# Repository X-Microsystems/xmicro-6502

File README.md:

# XMICRO-6502

W65C02 CPU card for the [XMICRO Bus](https://github.com/X-Microsystems/xmicro-bus).

Datasheet: [XMICRO-6502](Documentation/XMICRO-6502.pdf)

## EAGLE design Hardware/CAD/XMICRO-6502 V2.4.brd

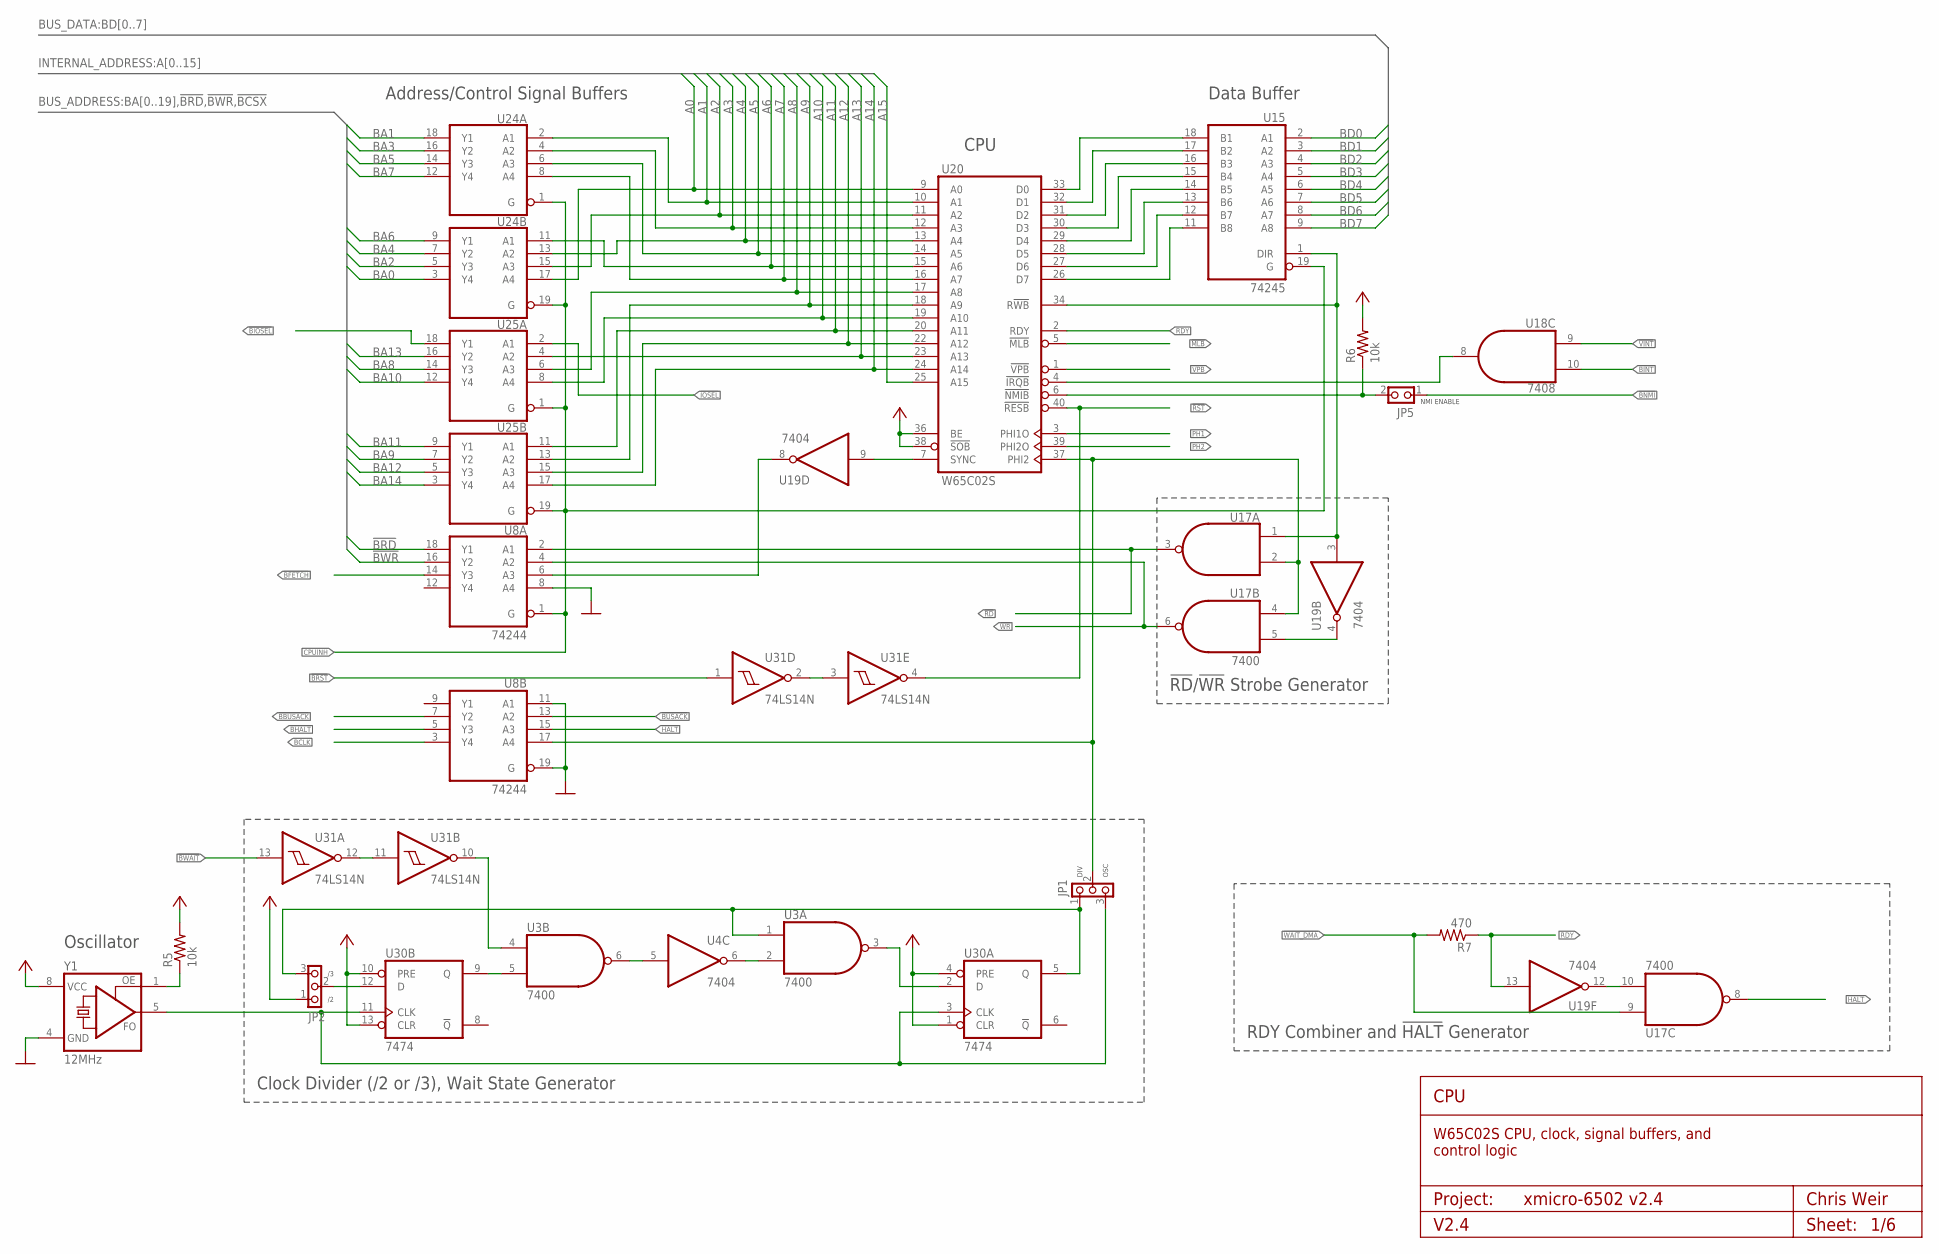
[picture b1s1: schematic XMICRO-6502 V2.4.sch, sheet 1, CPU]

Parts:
JP1, JP2: PINHD1X3THRU; 1X03
JP5: PINHD-1X2THRU; 1X02
R5, R6: 10k; 0207/10
R7: 470; 0207/10
U3, U17: 7400; DIL14
U4, U19: 7404; DIL14
U8, U24, U25: 74244; DIL20
U15: 74245; DIL20
U18: 7408; DIL14
U20: W65C02S; DIL40
U30: 7474; DIL14
U31: 74LS14N; DIL14
Y1: 12MHz; DIL08S

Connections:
!BBUSACK: U8.7 (Y2); also elsewhere on the board
!BFETCH: U8.14 (Y3); also elsewhere on the board
!BHALT: U8.5 (Y3); also elsewhere on the board
!BINT: U18.10 (I1); also elsewhere on the board
!BIOSEL: U25.18 (Y1); also elsewhere on the board
!BNMI: JP5.1; also elsewhere on the board
!BRD: U8.18 (Y1); also elsewhere on the board
!BRST: U31.1 (I); also elsewhere on the board
!BUSACK: U8.13 (A2); also elsewhere on the board
!BWAIT: U31.13 (I); also elsewhere on the board
!BWR: U8.16 (Y2); also elsewhere on the board
!CINT: U18.8 (O), U20.4 (!IRQB)
!HALT: U8.15 (A3), U17.8 (O); also elsewhere on the board
!IOSEL: U25.2 (A1); also elsewhere on the board
!MLB: U20.5 (!MLB); also elsewhere on the board
!RD: U8.2 (A1), U17.3 (O); also elsewhere on the board
!RST: U20.40 (!RESB), U31.4 (O); also elsewhere on the board
!VINT: U18.9 (I0); also elsewhere on the board
!VPB: U20.1 (!VPB); also elsewhere on the board
!WAIT_DMA: R7.2, U17.9 (I0); also elsewhere on the board
!WR: U8.4 (A2), U17.6 (O)
A0: U20.9 (A0), U24.17 (A4); also elsewhere on the board
A1: U20.10 (A1), U24.2 (A1); also elsewhere on the board
A2: U20.11 (A2), U24.15 (A3); also elsewhere on the board
A3: U20.12 (A3), U24.4 (A2)
A4: U20.13 (A4), U24.13 (A2)
A5: U20.14 (A5), U24.6 (A3)
A6: U20.15 (A6), U24.11 (A1)
A7: U20.16 (A7), U24.8 (A4)
A8: U20.17 (A8), U25.6 (A3)
A9: U20.18 (A9), U25.13 (A2); also elsewhere on the board
A10: U20.19 (A10), U25.8 (A4); also elsewhere on the board
A11: U20.20 (A11), U25.11 (A1); also elsewhere on the board
A12: U20.22 (A12), U25.15 (A3); also elsewhere on the board
A13: U20.23 (A13), U25.4 (A2); also elsewhere on the board
A14: U20.24 (A14), U25.17 (A4); also elsewhere on the board
A15: U20.25 (A15); also elsewhere on the board
BA0: U24.3 (Y4); also elsewhere on the board
BA1: U24.18 (Y1); also elsewhere on the board
BA2: U24.5 (Y3); also elsewhere on the board
BA3: U24.16 (Y2); also elsewhere on the board
BA4: U24.7 (Y2); also elsewhere on the board
BA5: U24.14 (Y3); also elsewhere on the board
BA6: U24.9 (Y1); also elsewhere on the board
BA7: U24.12 (Y4); also elsewhere on the board
BA8: U25.14 (Y3); also elsewhere on the board
BA9: U25.7 (Y2); also elsewhere on the board
BA10: U25.12 (Y4); also elsewhere on the board
BA11: U25.9 (Y1); also elsewhere on the board
BA12: U25.5 (Y3); also elsewhere on the board
BA13: U25.16 (Y2); also elsewhere on the board
BA14: U25.3 (Y4); also elsewhere on the board
BCLK: U8.3 (Y4); also elsewhere on the board
BD0: U15.2 (A1); also elsewhere on the board
BD1: U15.3 (A2); also elsewhere on the board
BD2: U15.4 (A3); also elsewhere on the board
BD3: U15.5 (A4); also elsewhere on the board
BD4: U15.6 (A5); also elsewhere on the board
BD5: U15.7 (A6); also elsewhere on the board
BD6: U15.8 (A7); also elsewhere on the board
BD7: U15.9 (A8); also elsewhere on the board
CPUINH: U8.1 (G), U15.19 (G), U24.1 (G), U24.19 (G), U25.1 (G), U25.19 (G); also elsewhere on the board
GND: U3.7 (GND), U4.7 (GND), U8.8 (A4), U8.10 (GND), U8.11 (A1), U8.19 (G), U15.10 (GND), U17.7 (GND), U18.7 (GND), U19.7 (GND), U20.21 (GND), U24.10 (GND), U25.10 (GND), U30.7 (GND), U31.7 (GND), Y1.4 (GND); also elsewhere on the board
unnamed: JP2.2, U30.12 (D)
unnamed: U17.5 (I1), U19.4 (O)
unnamed: JP1.1, JP2.3, U3.1 (I0), U30.5 (Q)
unnamed: U15.1 (DIR), U17.1 (I0), U19.3 (I), U20.34 (R!WB)
unnamed: U3.5 (I1), U30.9 (Q)
unnamed: U3.6 (O), U4.5 (I)
unnamed: R5.1, Y1.1 (OE)
unnamed: U17.10 (I1), U19.12 (O)
unnamed: U3.2 (I1), U4.6 (O)
unnamed: U15.11 (B8), U20.26 (D7)
unnamed: U15.12 (B7), U20.27 (D6)
unnamed: U15.13 (B6), U20.28 (D5)
unnamed: U15.14 (B5), U20.29 (D4)
unnamed: U15.15 (B4), U20.30 (D3)
unnamed: U15.16 (B3), U20.31 (D2)
unnamed: U15.17 (B2), U20.32 (D1)
unnamed: U15.18 (B1), U20.33 (D0)
unnamed: U31.11 (I), U31.12 (O)
unnamed: JP5.2, R6.1, U20.6 (!NMIB)
unnamed: U3.3 (O), U30.2 (D)
unnamed: JP1.3, U30.3 (CLK), U30.11 (CLK), Y1.5 (FO)
unnamed: U19.9 (I), U20.7 (SYNC)
unnamed: U8.6 (A3), U19.8 (O)
unnamed: U3.4 (I0), U31.10 (O)
unnamed: U31.2 (O), U31.3 (I)
PH0: JP1.2, U8.17 (A4), U17.2 (I1), U17.4 (I0), U20.37 (PHI2)
PH1: U20.3 (PHI1O); also elsewhere on the board
PH2: U20.39 (PHI2O); also elsewhere on the board
RDY: R7.1, U19.13 (I), U20.2 (RDY)
VCC: JP2.1, R5.2, R6.2, U3.14 (VCC), U4.14 (VCC), U8.20 (VCC), U15.20 (VCC), U17.14 (VCC), U18.14 (VCC), U19.14 (VCC), U20.8 (VCC), U20.36 (BE), U20.38 (!SOB), U24.20 (VCC), U25.20 (VCC), U30.1 (CLR), U30.4 (PRE), U30.10 (PRE), U30.13 (CLR), U30.14 (VCC), U31.14 (VCC), Y1.8 (VCC); also elsewhere on the board

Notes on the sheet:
Project:
CPU
V2.4
Chris Weir
Sheet:
W65C02S CPU, clock, signal buffers, and control logic
Address/Control Signal Buffers
Data Buffer
!RD!/!WR! Strobe Generator
Oscillator
RDY Combiner and !HALT! Generator
Clock Divider (/2 or /3), Wait State Generator
DIV
OSC
NMI ENABLE

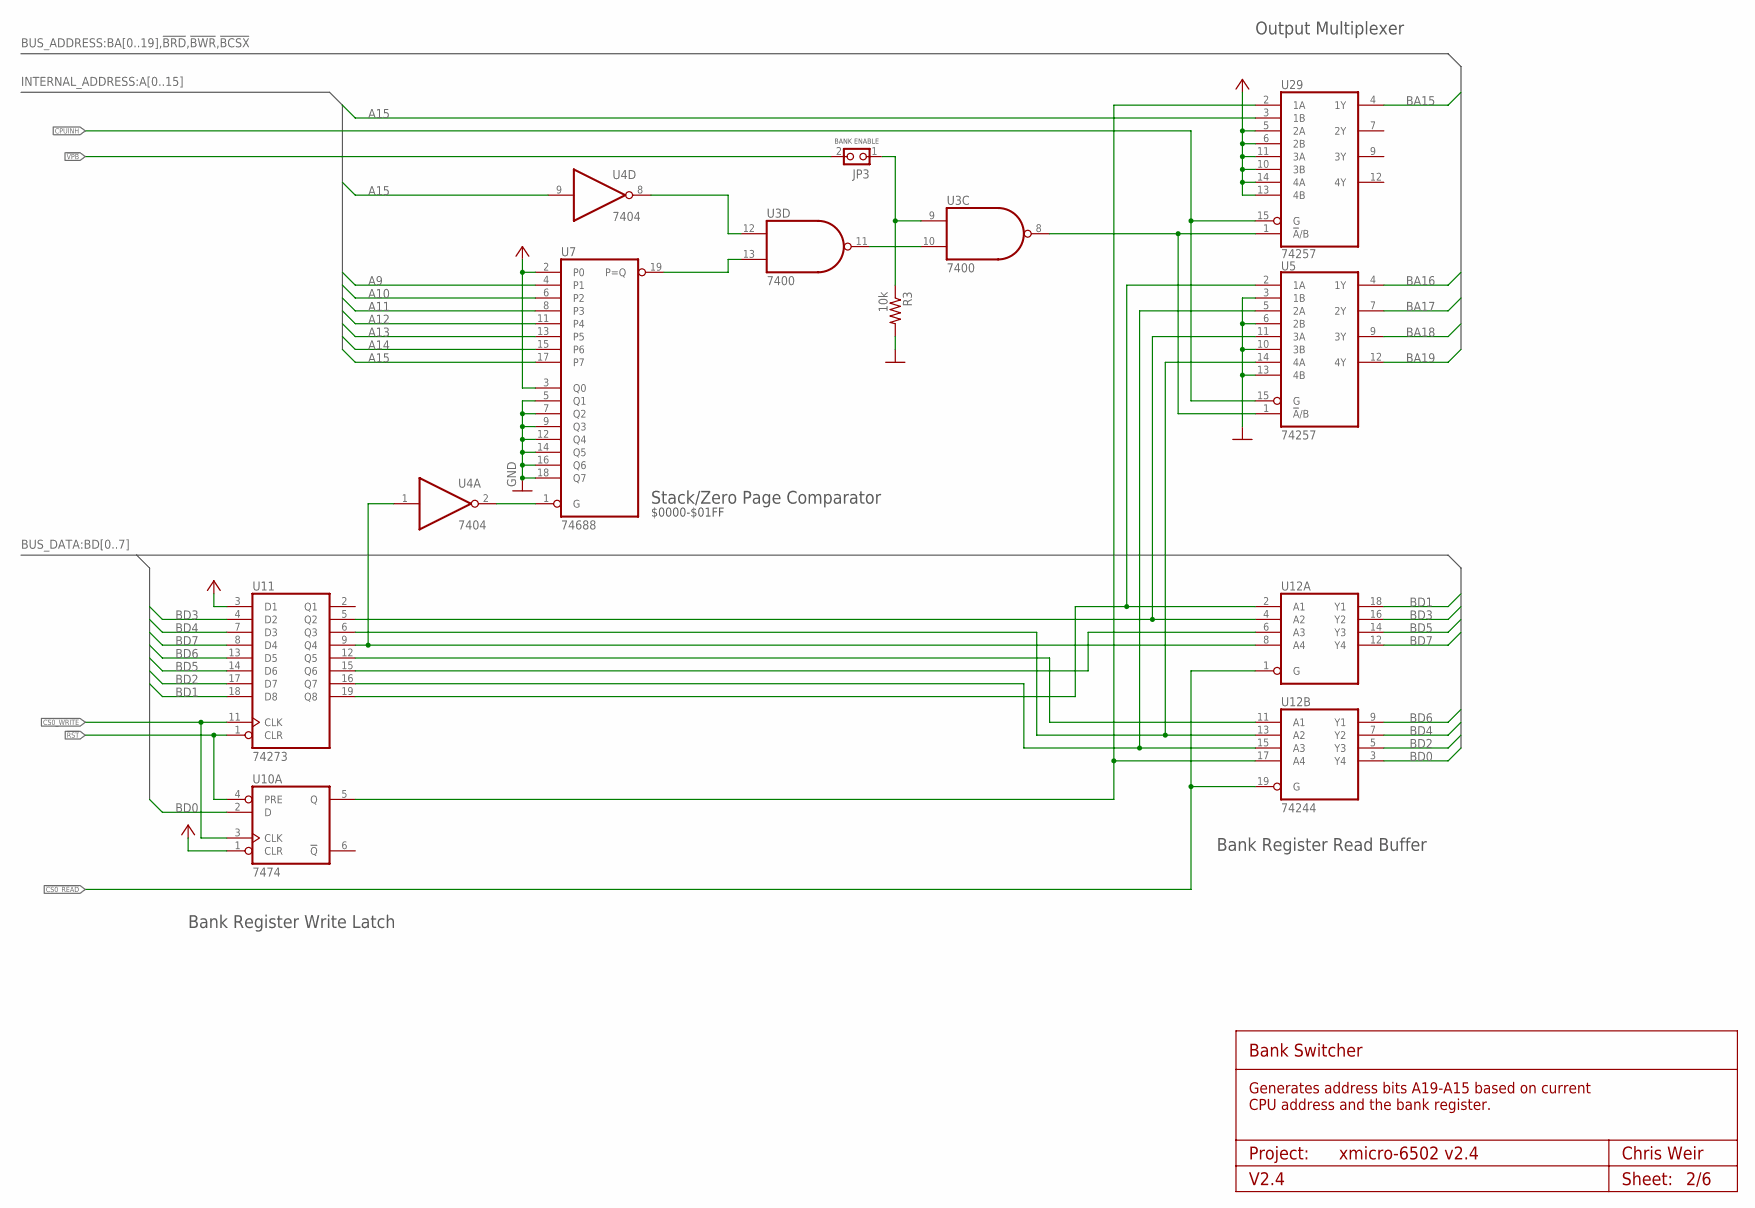
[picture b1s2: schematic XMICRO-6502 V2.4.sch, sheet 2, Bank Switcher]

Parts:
JP3: PINHD-1X2THRU; 1X02
R3: 10k; 0207/10
U3: 7400; DIL14
U4: 7404; DIL14
U5, U29: 74257; DIL16
U7: 74688; DIL20
U10: 7474; DIL14
U11: 74273; DIL20
U12: 74244; DIL20

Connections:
!CS0_READ: U12.1 (G), U12.19 (G); also elsewhere on the board
!CS0_WRITE: U10.3 (CLK), U11.11 (CLK); also elsewhere on the board
!RST: U10.4 (PRE), U11.1 (CLR); also elsewhere on the board
!VPB: JP3.2; also elsewhere on the board
A9: U7.4 (P1); also elsewhere on the board
A10: U7.6 (P2); also elsewhere on the board
A11: U7.8 (P3); also elsewhere on the board
A12: U7.11 (P4); also elsewhere on the board
A13: U7.13 (P5); also elsewhere on the board
A14: U7.15 (P6); also elsewhere on the board
A15: U4.9 (I), U7.17 (P7), U29.3 (1B); also elsewhere on the board
BA15: U29.4 (1Y); also elsewhere on the board
BA16: U5.4 (1Y); also elsewhere on the board
BA17: U5.7 (2Y); also elsewhere on the board
BA18: U5.9 (3Y); also elsewhere on the board
BA19: U5.12 (4Y); also elsewhere on the board
BD0: U10.2 (D), U12.3 (Y4); also elsewhere on the board
BD1: U11.18 (D8), U12.18 (Y1); also elsewhere on the board
BD2: U11.17 (D7), U12.5 (Y3); also elsewhere on the board
BD3: U11.4 (D2), U12.16 (Y2); also elsewhere on the board
BD4: U11.7 (D3), U12.7 (Y2); also elsewhere on the board
BD5: U11.14 (D6), U12.14 (Y3); also elsewhere on the board
BD6: U11.13 (D5), U12.9 (Y1); also elsewhere on the board
BD7: U11.8 (D4), U12.12 (Y4); also elsewhere on the board
CPUINH: U5.15 (G), U29.15 (G); also elsewhere on the board
GND: R3.2, U3.7 (GND), U4.7 (GND), U5.3 (1B), U5.6 (2B), U5.8 (GND), U5.10 (3B), U5.13 (4B), U7.5 (Q1), U7.7 (Q2), U7.9 (Q3), U7.10 (GND), U7.12 (Q4), U7.14 (Q5), U7.16 (Q6), U7.18 (Q7), U10.7 (GND), U11.10 (GND), U12.10 (GND), U29.8 (GND); also elsewhere on the board
unnamed: U5.2 (1A), U11.19 (Q8), U12.2 (A1)
unnamed: U5.11 (3A), U11.5 (Q2), U12.4 (A2)
unnamed: U5.5 (2A), U11.16 (Q7), U12.15 (A3)
unnamed: U5.14 (4A), U11.6 (Q3), U12.13 (A2)
unnamed: U3.12 (I0), U4.8 (O)
unnamed: U3.13 (I1), U7.19 (P=Q)
unnamed: U10.5 (Q), U12.17 (A4), U29.2 (1A)
unnamed: U3.10 (I1), U3.11 (O)
unnamed: JP3.1, R3.1, U3.9 (I0)
unnamed: U11.15 (Q6), U12.6 (A3)
unnamed: U3.8 (O), U5.1 (!A!/B), U29.1 (!A!/B)
unnamed: U11.12 (Q5), U12.11 (A1)
unnamed: U4.1 (I), U11.9 (Q4), U12.8 (A4)
unnamed: U4.2 (O), U7.1 (G)
VCC: U3.14 (VCC), U4.14 (VCC), U5.16 (VCC), U7.2 (P0), U7.3 (Q0), U7.20 (VCC), U10.1 (CLR), U10.14 (VCC), U11.3 (D1), U11.20 (VCC), U12.20 (VCC), U29.5 (2A), U29.6 (2B), U29.10 (3B), U29.11 (3A), U29.13 (4B), U29.14 (4A), U29.16 (VCC); also elsewhere on the board

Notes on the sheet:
$0000-$01FF
Bank Register Read Buffer
Bank Register Write Latch
Stack/Zero Page Comparator
Bank Switcher
Generates address bits A19-A15 based on current CPU address and the bank register.
Output Multiplexer
Project:
V2.4
Chris Weir
Sheet:
BANK ENABLE

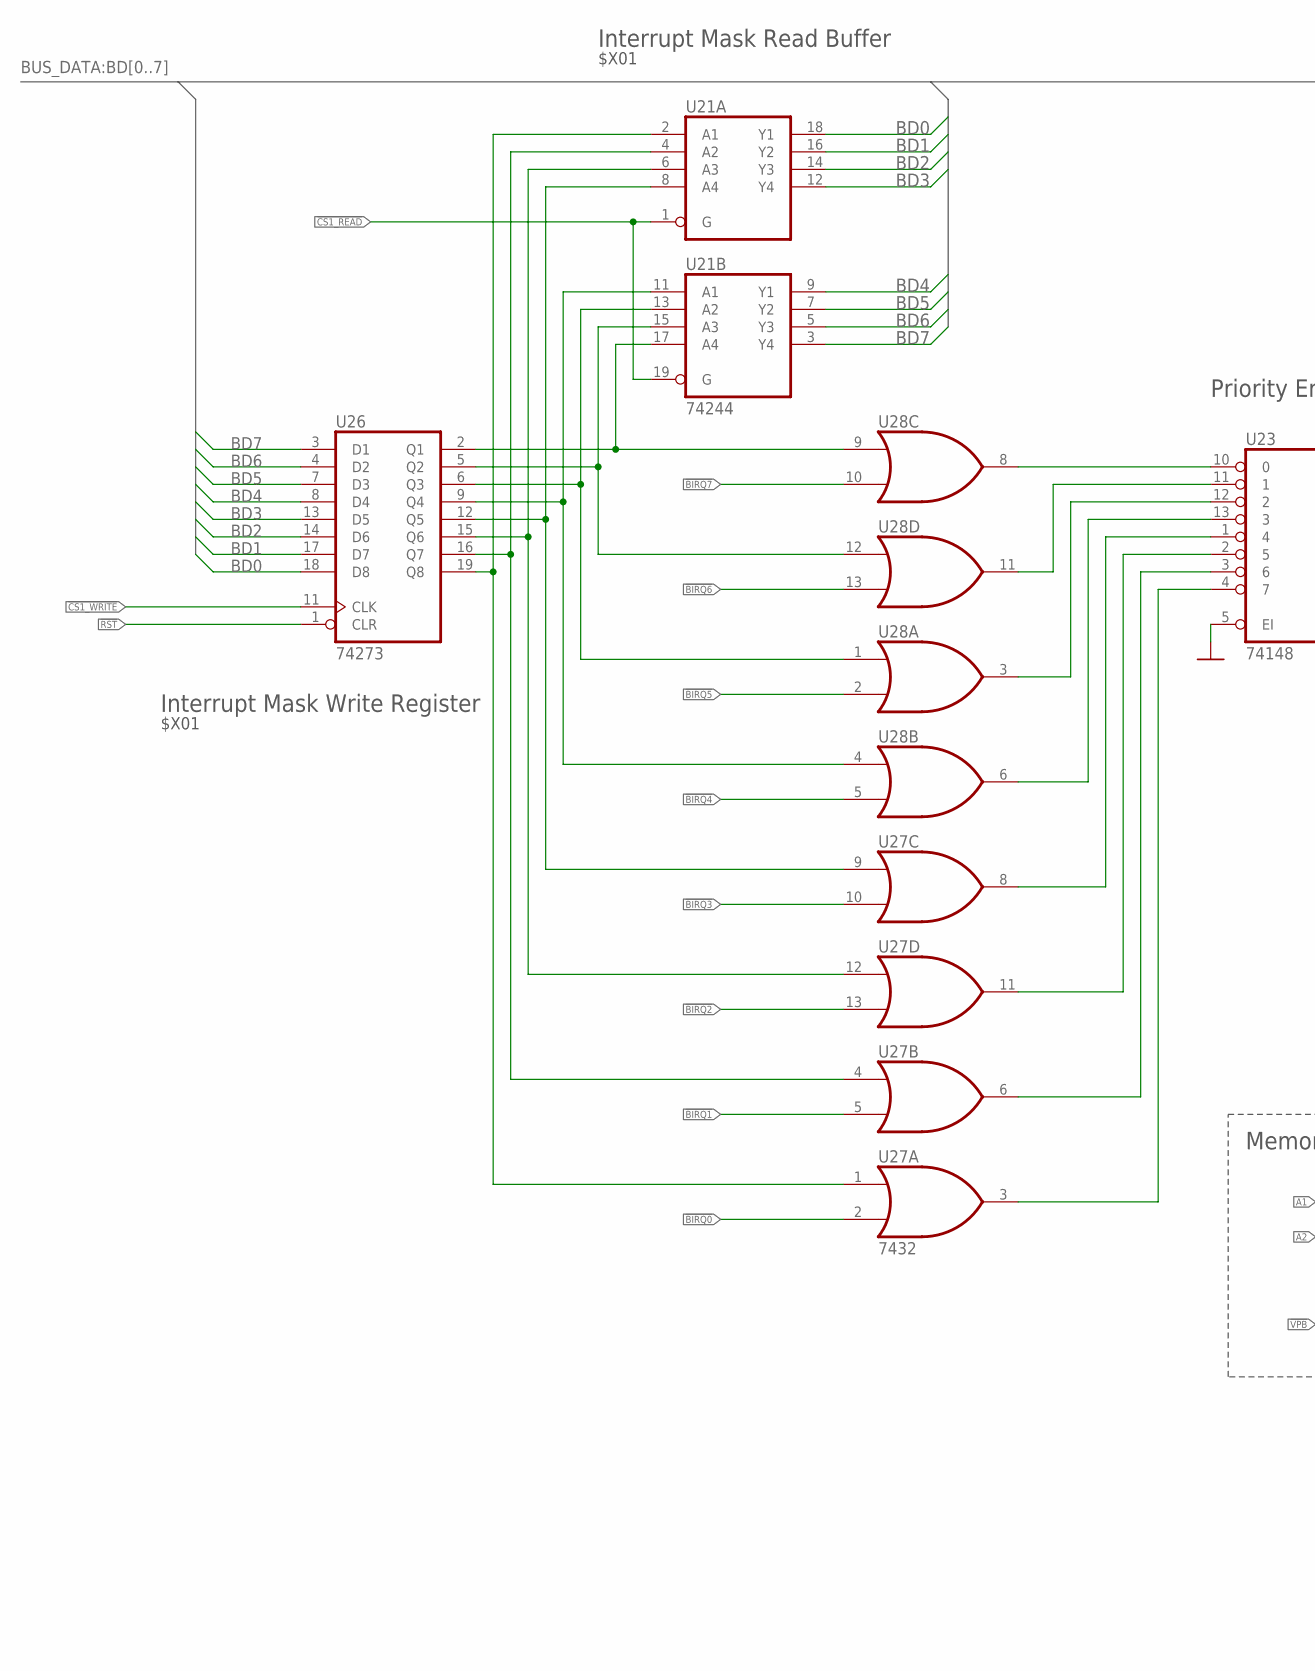
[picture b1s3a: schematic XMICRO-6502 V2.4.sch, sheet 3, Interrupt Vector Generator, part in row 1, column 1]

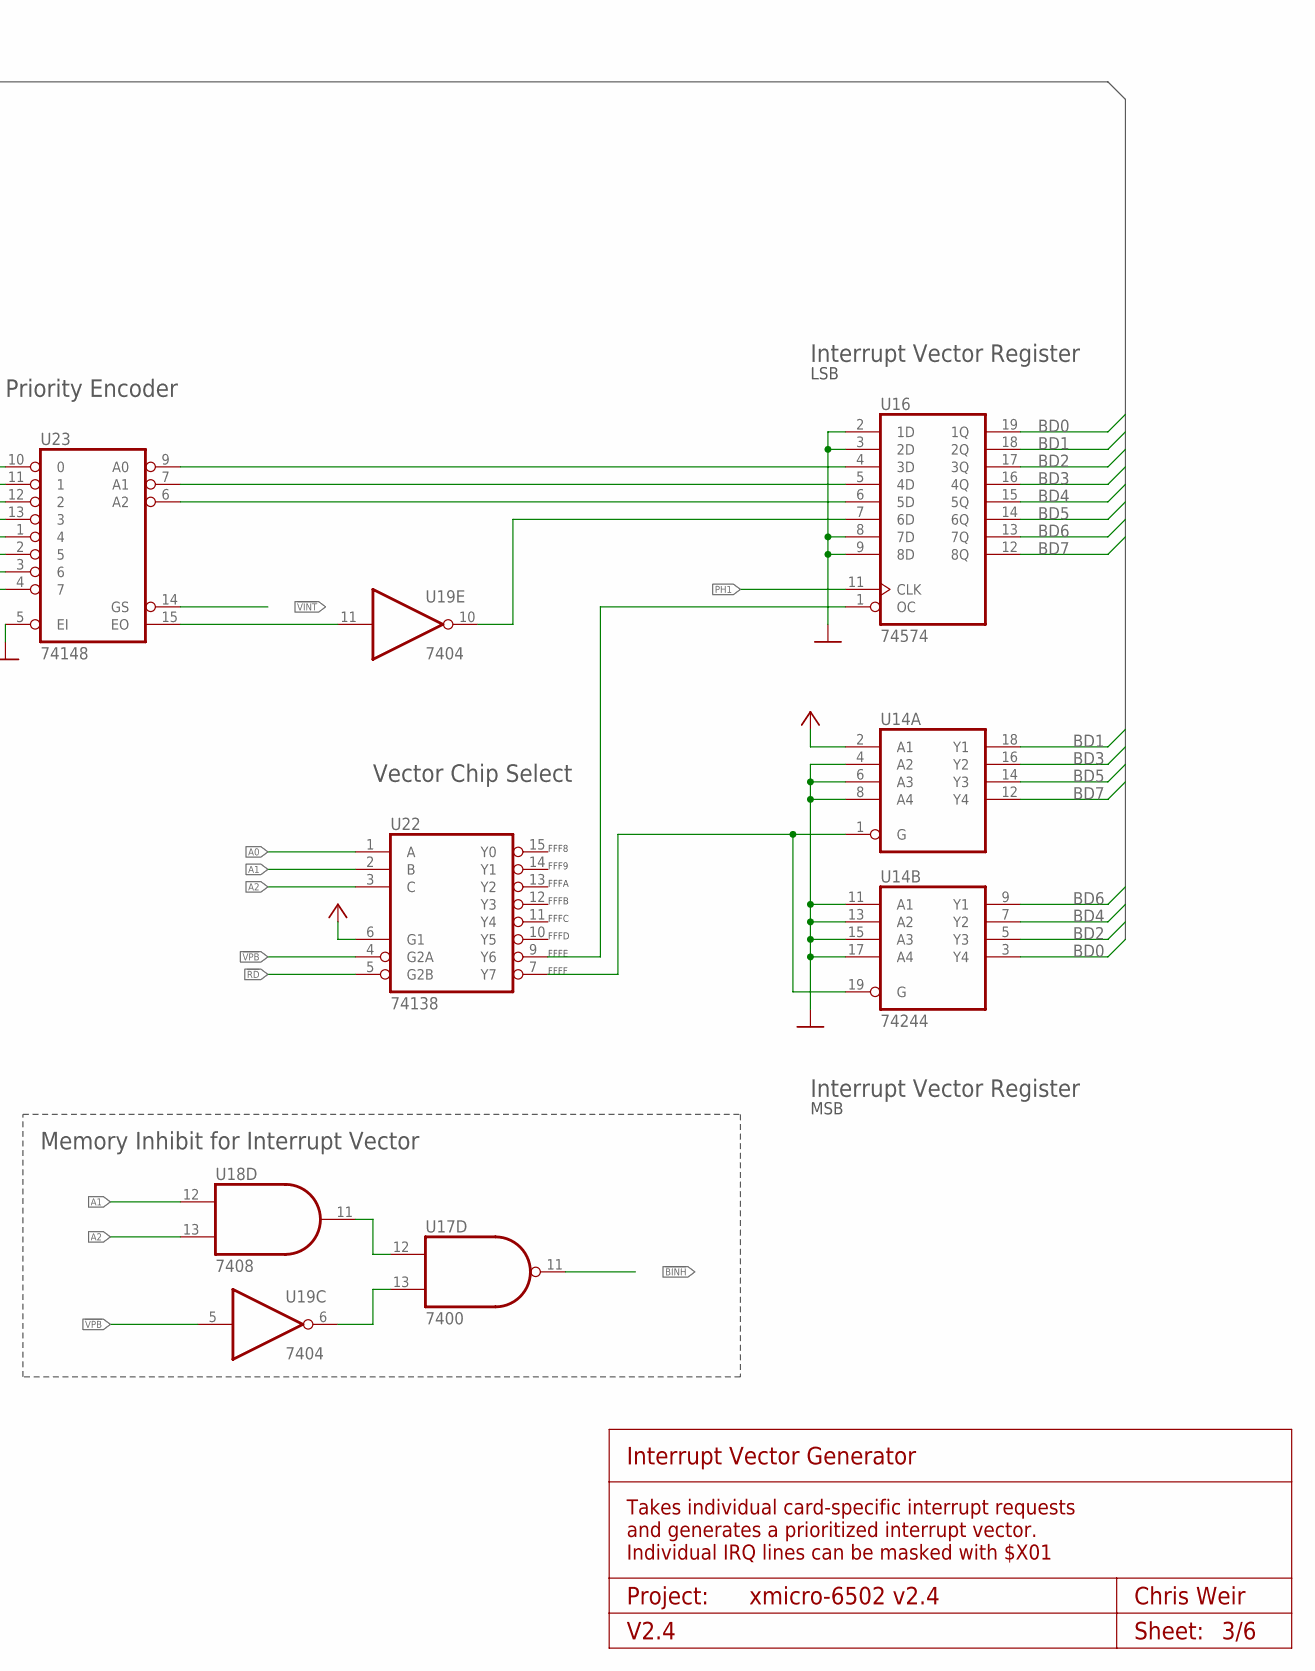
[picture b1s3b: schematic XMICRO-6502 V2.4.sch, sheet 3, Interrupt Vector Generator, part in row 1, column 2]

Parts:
U14, U21: 74244; DIL20
U16: 74574; DIL20
U17: 7400; DIL14
U18: 7408; DIL14
U19: 7404; DIL14
U22: 74138; DIL16
U23: 74148; DIL16
U26: 74273; DIL20
U27, U28: 7432; DIL14

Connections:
!BINH: U17.11 (O); also elsewhere on the board
!BIRQ0: U27.2 (I1); also elsewhere on the board
!BIRQ1: U27.5 (I1); also elsewhere on the board
!BIRQ2: U27.13 (I1); also elsewhere on the board
!BIRQ3: U27.10 (I1); also elsewhere on the board
!BIRQ4: U28.5 (I1); also elsewhere on the board
!BIRQ5: U28.2 (I1); also elsewhere on the board
!BIRQ6: U28.13 (I1); also elsewhere on the board
!BIRQ7: U28.10 (I1); also elsewhere on the board
!CS1_READ: U21.1 (G), U21.19 (G); also elsewhere on the board
!CS1_WRITE: U26.11 (CLK); also elsewhere on the board
!IVP: U16.1 (OC), U22.9 (Y6)
!RD: U22.5 (G2B); also elsewhere on the board
!RST: U26.1 (CLR); also elsewhere on the board
!VINT: U23.14 (GS); also elsewhere on the board
!VPB: U19.5 (I), U22.4 (G2A); also elsewhere on the board
A0: U22.1 (A); also elsewhere on the board
A1: U18.12 (I0), U22.2 (B); also elsewhere on the board
A2: U18.13 (I1), U22.3 (C); also elsewhere on the board
BD0: U14.3 (Y4), U16.19 (1Q), U21.18 (Y1), U26.18 (D8); also elsewhere on the board
BD1: U14.18 (Y1), U16.18 (2Q), U21.16 (Y2), U26.17 (D7); also elsewhere on the board
BD2: U14.5 (Y3), U16.17 (3Q), U21.14 (Y3), U26.14 (D6); also elsewhere on the board
BD3: U14.16 (Y2), U16.16 (4Q), U21.12 (Y4), U26.13 (D5); also elsewhere on the board
BD4: U14.7 (Y2), U16.15 (5Q), U21.9 (Y1), U26.8 (D4); also elsewhere on the board
BD5: U14.14 (Y3), U16.14 (6Q), U21.7 (Y2), U26.7 (D3); also elsewhere on the board
BD6: U14.9 (Y1), U16.13 (7Q), U21.5 (Y3), U26.4 (D2); also elsewhere on the board
BD7: U14.12 (Y4), U16.12 (8Q), U21.3 (Y4), U26.3 (D1); also elsewhere on the board
GND: U14.4 (A2), U14.6 (A3), U14.8 (A4), U14.10 (GND), U14.11 (A1), U14.13 (A2), U14.15 (A3), U14.17 (A4), U16.2 (1D), U16.3 (2D), U16.8 (7D), U16.9 (8D), U16.10 (GND), U17.7 (GND), U18.7 (GND), U19.7 (GND), U21.10 (GND), U22.8 (GND), U23.5 (EI), U23.8 (GND), U26.10 (GND), U27.7 (GND), U28.7 (GND); also elsewhere on the board
unnamed: U16.4 (3D), U23.9 (A0)
unnamed: U16.5 (4D), U23.7 (A1)
unnamed: U19.11 (I), U23.15 (EO)
unnamed: U17.13 (I1), U19.6 (O)
unnamed: U14.1 (G), U14.19 (G), U22.7 (Y7)
unnamed: U16.6 (5D), U23.6 (A2)
unnamed: U17.12 (I0), U18.11 (O)
unnamed: U23.10 (0), U28.8 (O)
unnamed: U16.7 (6D), U19.10 (O)
unnamed: U23.11 (1), U28.11 (O)
unnamed: U23.12 (2), U28.3 (O)
unnamed: U23.13 (3), U28.6 (O)
unnamed: U23.1 (4), U27.8 (O)
unnamed: U23.2 (5), U27.11 (O)
unnamed: U23.3 (6), U27.6 (O)
unnamed: U23.4 (7), U27.3 (O)
unnamed: U21.17 (A4), U26.2 (Q1), U28.9 (I0)
unnamed: U21.15 (A3), U26.5 (Q2), U28.12 (I0)
unnamed: U21.13 (A2), U26.6 (Q3), U28.1 (I0)
unnamed: U21.11 (A1), U26.9 (Q4), U28.4 (I0)
unnamed: U21.8 (A4), U26.12 (Q5), U27.9 (I0)
unnamed: U21.6 (A3), U26.15 (Q6), U27.12 (I0)
unnamed: U21.4 (A2), U26.16 (Q7), U27.4 (I0)
unnamed: U21.2 (A1), U26.19 (Q8), U27.1 (I0)
PH1: U16.11 (CLK); also elsewhere on the board
VCC: U14.2 (A1), U14.20 (VCC), U16.20 (VCC), U17.14 (VCC), U18.14 (VCC), U19.14 (VCC), U21.20 (VCC), U22.6 (G1), U22.16 (VCC), U23.16 (VCC), U26.20 (VCC), U27.14 (VCC), U28.14 (VCC); also elsewhere on the board

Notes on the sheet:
FFF8
FFF9
FFFA
FFFB
FFFC
FFFD
FFFE
FFFF
LSB
Interrupt Vector Generator
Takes individual card-specific interrupt requests and generates a prioritized interrupt vector. Individual IRQ lines can be masked with $X01
$X01
Interrupt Mask Write Register
Interrupt Mask Read Buffer
Interrupt Vector Register
MSB
Priority Encoder
Vector Chip Select
Memory Inhibit for Interrupt Vector
Project:
V2.4
Chris Weir
Sheet:

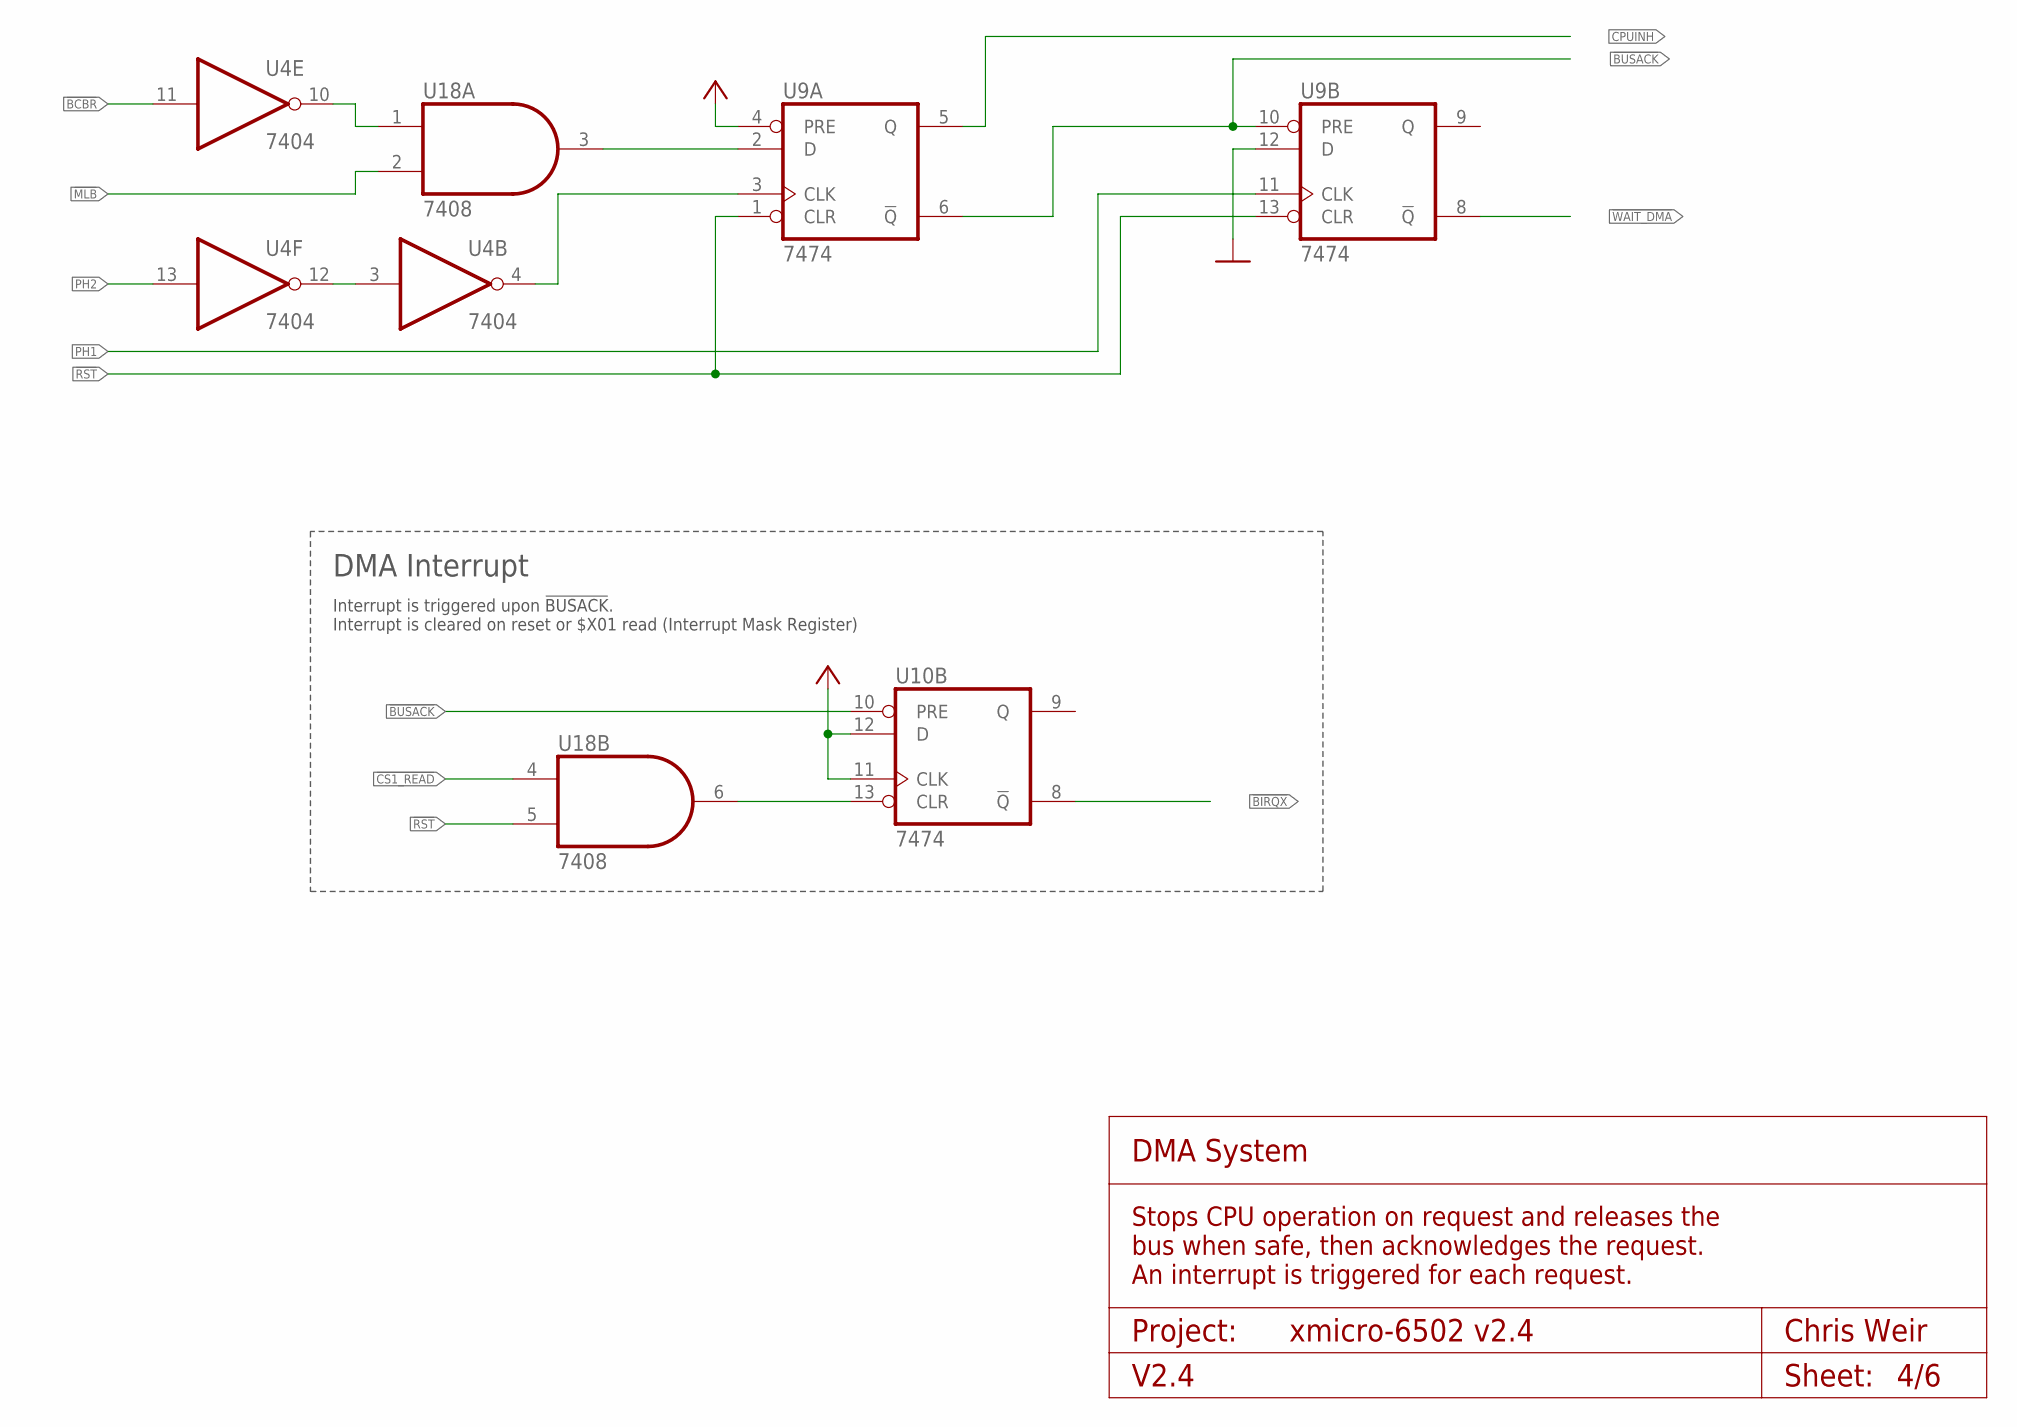
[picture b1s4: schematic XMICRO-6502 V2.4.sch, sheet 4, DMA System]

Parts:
U4: 7404; DIL14
U9, U10: 7474; DIL14
U18: 7408; DIL14

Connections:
!BCBR: U4.11 (I); also elsewhere on the board
!BIRQX: U10.8 (!Q); also elsewhere on the board
!BUSACK: U9.6 (!Q), U9.10 (PRE), U10.10 (PRE); also elsewhere on the board
!CS1_READ: U18.4 (I0); also elsewhere on the board
!MLB: U18.2 (I1); also elsewhere on the board
!RST: U9.1 (CLR), U9.13 (CLR), U18.5 (I1); also elsewhere on the board
!WAIT_DMA: U9.8 (!Q); also elsewhere on the board
CPUINH: U9.5 (Q); also elsewhere on the board
GND: U4.7 (GND), U9.7 (GND), U9.12 (D), U10.7 (GND), U18.7 (GND); also elsewhere on the board
unnamed: U9.2 (D), U18.3 (O)
unnamed: U10.13 (CLR), U18.6 (O)
unnamed: U4.10 (O), U18.1 (I0)
unnamed: U4.3 (I), U4.12 (O)
unnamed: U4.4 (O), U9.3 (CLK)
PH1: U9.11 (CLK); also elsewhere on the board
PH2: U4.13 (I); also elsewhere on the board
VCC: U4.14 (VCC), U9.4 (PRE), U9.14 (VCC), U10.11 (CLK), U10.12 (D), U10.14 (VCC), U18.14 (VCC); also elsewhere on the board

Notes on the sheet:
Interrupt is triggered upon !BUSACK!. Interrupt is cleared on reset or $X01 read (Interrupt Mask Register)
DMA System
Stops CPU operation on request and releases the bus when safe, then acknowledges the request. An interrupt is triggered for each request.
DMA Interrupt
Project:
V2.4
Chris Weir
Sheet:

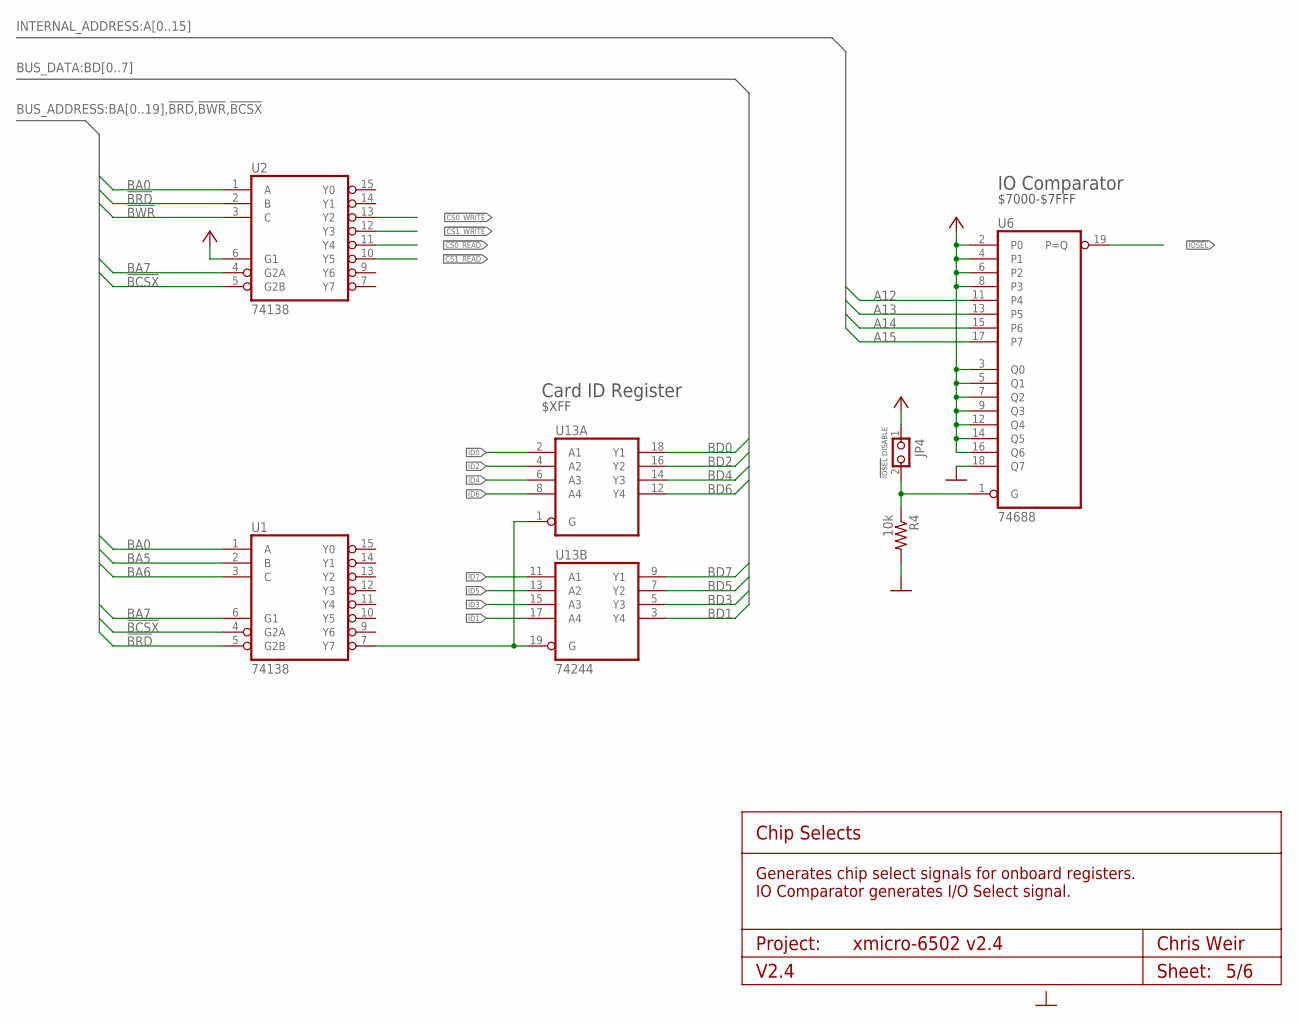
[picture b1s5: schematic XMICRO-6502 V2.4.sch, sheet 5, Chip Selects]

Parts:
JP4: PINHD-1X2THRU; 1X02
R4: 10k; 0207/10
U1, U2: 74138; DIL16
U6: 74688; DIL20
U13: 74244; DIL20

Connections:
!BCSX: U1.4 (G2A), U2.5 (G2B); also elsewhere on the board
!BRD: U1.5 (G2B), U2.2 (B); also elsewhere on the board
!BWR: U2.3 (C); also elsewhere on the board
!CS0_READ: U2.11 (Y4); also elsewhere on the board
!CS0_WRITE: U2.13 (Y2); also elsewhere on the board
!CS1_READ: U2.10 (Y5); also elsewhere on the board
!CS1_WRITE: U2.12 (Y3); also elsewhere on the board
!IOSEL: U6.19 (P=Q); also elsewhere on the board
A12: U6.11 (P4); also elsewhere on the board
A13: U6.13 (P5); also elsewhere on the board
A14: U6.15 (P6); also elsewhere on the board
A15: U6.17 (P7); also elsewhere on the board
BA0: U1.1 (A), U2.1 (A); also elsewhere on the board
BA5: U1.2 (B); also elsewhere on the board
BA6: U1.3 (C); also elsewhere on the board
BA7: U1.6 (G1), U2.4 (G2A); also elsewhere on the board
BD0: U13.18 (Y1); also elsewhere on the board
BD1: U13.3 (Y4); also elsewhere on the board
BD2: U13.16 (Y2); also elsewhere on the board
BD3: U13.5 (Y3); also elsewhere on the board
BD4: U13.14 (Y3); also elsewhere on the board
BD5: U13.7 (Y2); also elsewhere on the board
BD6: U13.12 (Y4); also elsewhere on the board
BD7: U13.9 (Y1); also elsewhere on the board
GND: R4.2, U1.8 (GND), U2.8 (GND), U6.10 (GND), U6.18 (Q7), U13.10 (GND); also elsewhere on the board
ID0: U13.2 (A1)
ID1: U13.17 (A4)
ID2: U13.4 (A2)
ID3: U13.15 (A3)
ID4: U13.6 (A3)
ID5: U13.13 (A2)
ID6: U13.8 (A4)
ID7: U13.11 (A1)
unnamed: JP4.2, R4.1, U6.1 (G)
unnamed: U1.7 (Y7), U13.1 (G), U13.19 (G)
VCC: JP4.1, U1.16 (VCC), U2.6 (G1), U2.16 (VCC), U6.2 (P0), U6.3 (Q0), U6.4 (P1), U6.5 (Q1), U6.6 (P2), U6.7 (Q2), U6.8 (P3), U6.9 (Q3), U6.12 (Q4), U6.14 (Q5), U6.16 (Q6), U6.20 (VCC), U13.20 (VCC); also elsewhere on the board

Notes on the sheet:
Chip Selects
Generates chip select signals for onboard registers. IO Comparator generates I/O Select signal.
$XFF
Card ID Register
Project:
V2.4
Chris Weir
Sheet:
$7000-$7FFF
IO Comparator
!IOSEL! DISABLE
